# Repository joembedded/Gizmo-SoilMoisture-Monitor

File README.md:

# Gizmo - 'GiessMonitor' #
**Ein LowCost IoT Sensor zur Messung der Bodenfeuchte mit LoRa und/oder SDI-12/BluetoothLE**

Es gibt unzählige Ultra-LowCost-Sensoren zur Messung der Bodenfeuchte.
Die meisten davon taugen aber oft nicht einmal für Hobby-Zwecke.

Das Projekt Gizmo - 'GiessMonitor' möchte einen einfachen, aber trotzdem
für die Praxis geeigneten IoT Sensor entwickeln. Final soll ein LoRa-Modul
eingesetzt werden, so dass Gizmo auch über grosse Entfernungen und selbst mit
einfachen Batterien jahrelang arbeiten kann. 

_*Gizmo ist ein 100% Open Source Projekt!*_
_*Wenn alles klappt, könnte daraus ein spannender und preisgünstiger Sensor für die Allgemeinheit werden.*_
_*'Collaborteure' sind jederzeit herzlich willkommen!*_

---
**Gizmo_0V15 - Boilerplate und Vor-Prototyp**

Im ersten Schritt geht es aber erst einmal darum das Messverfahren festzulegen.

Es bietet sich an die recht hohe Dielektrizitätskonstante von Wasser auszunutzen. 
Diese ist bis ca. 1 GHz recht konstant (bei ca. 80), hat aber den Nachteil, dass z.B. Salze bei
niedereren Frequenzen (unter ca. 1-10 Mhz) das Signal stark verfälschen.
(Details dazu: [Permitivität von mineralisiertem Wasser](https://de.wikipedia.org/wiki/Permittivit%C3%A4t). Die Permitivität setzt sich aus der 
Dielektrizitätskonstante (Realteil) und dem störenden Leitwert (Imaginärteil) zusammen).

(Technische Anmerkung: Die Menge des vorhandenen Wassers im Boden ist allerdings trotzdem auch immer nur ein indirektes Mass für den 'Giess-Bedarf',
denn die Art des Bodens (z.B. sandig oder eher lehmig) spielt eine fast noch größere Rolle. Aber da diese sich lokal normalerweise nicht ändert,
ist der Wassergehalt als Messwert absolut OK. Auch ist der Salzgehalt nicht von Interesse, einzig nur sollte er das Signal möglichst wenig verfälschen.
Gizmo soll ja auch kein wissenschaftliches Messgerät, sondern nur ein (hoffentlich) zuverlässiger Giess-Monitor werden).

Es bietet sich also an, Frequenzen im Bereich > 10 Mhz und < 1Ghz zu verwenden. Als Sensorelement wird die Kapazität einer kleinen 
Kupferfläche (die in einer korrosionsgeschützten Innenlage der PCB geschützt ist) verwendet und ungefähr ca. 10pF - 80pF beträgt.
Je stärker das Anregungssignal ist, desto günstiger wird auch die Messung. Aber schnell kann daraus auch ein nicht CE-konformer Sender werden.

Nach wissenschaftlichen Referenzstudien vergleichbarer Sensoren (u.a. [Measurement of Soil Water Content with a 50-MHz Soil Dielectric Sensor](https://www.researchgate.net/publication/43261344_Measurement_of_Soil_Water_Content_with_a_50-MHz_Soil_Dielectric_Sensor) ) eignet sich das weltweit freie ISM-Band 40.660 – 40.700 MHz dazu sehr gut. In Deutschland sind hier bis zu 10 mW Sendeleistung erlaubt ([SRD Verfügung](https://www.bundesnetzagentur.de/SharedDocs/Downloads/DE/Sachgebiete/Telekommunikation/Unternehmen_Institutionen/Frequenzen/Allgemeinzuteilungen/FunkanlagenGeringerReichweite/2018_05_SRD_pdf.pdf?__blob=publicationFile&v=1)).

Die Geometrie der Sensorfläche muss für einen kapazitiven Sensor aber jedezeit unter der Lambda/4-Länge liegen, bei einer max. Dielektrizitätskonstante von 80 wären das bei 40 Mhz ca. 21 cm. Eine erste Simulation mit FEMM ergab ca. 10 cm als gut geeignet. Die Kupferflächen werden korrosionsgeschützt symetrisch auf den beiden Innenlagen platziert, Details zur Geometrie im Schaltplan.

[Sensorsimulation](./docu/sensorsim01.png) die erste mit FEMM simulierte Geometrie kam dem Ergebnis schon recht nahe.

Die Frage war auch, ob das 40 Mhz Signal störende Oberwellen abstrahlt (diese sind in der DIN EN 55011 / CISPR 11 definiert). Eine Freifeld-Messung ergab aber keinerlei Auffälligkeiten, selbst auf der Grundfrequenz ist die Abstrahlung noch leicht unterm allgemeinen Grenzwert, wenn also ein 40.68 MHz Oszillator verwendet wird, ist Gizmo in jedem Fall absolut im erlaubten Bereich (der Grenzwert für SRD ist bei ca. 105 dBµV/m): [EMV Bewertung](./docu/emv_girmo_pre.png).

  Die erste Version arbeitet mit SDI-12 und Bluetooth (Modul: [Open-SDI12-Blue](https://github.com/joembedded/Open-SDI12-Blue) )

[Gizmo_0V1 - PCB, Layouts und Schaltpläne im Ordner 'docu'](./docu/)

---
**Gizmo - der Plan**
- Tests und Festlegung des Messsystems: Dazu PCB mit SDI-12 und Bluetooth.
- Erste Software (basierend auf Open-SDI12-Blue-Libs und JesFs)
- Finalisierung V1.0 mit LoRa-Modul und 3D-gedrucktem Batteriefach
- Problemlose Anbindung an z.B. das Community LoRa-Netz TTN oder ChirpStack
- ...

---
## Changelog  ##
- 01.04.2023 V0.01 Gizmo Prototyp als PCB in Fertigung gegeben
- 07.04.2023 Erste elektrische Tests der PCB V0.01
- 15.05.2025 Gizmo V0.15 als SDI-12 Sensor und mit Bluetooth 
- 18.07.2025 RAK3172LP: erste Prototypen mit KiCAD Breakout-Board OK
---

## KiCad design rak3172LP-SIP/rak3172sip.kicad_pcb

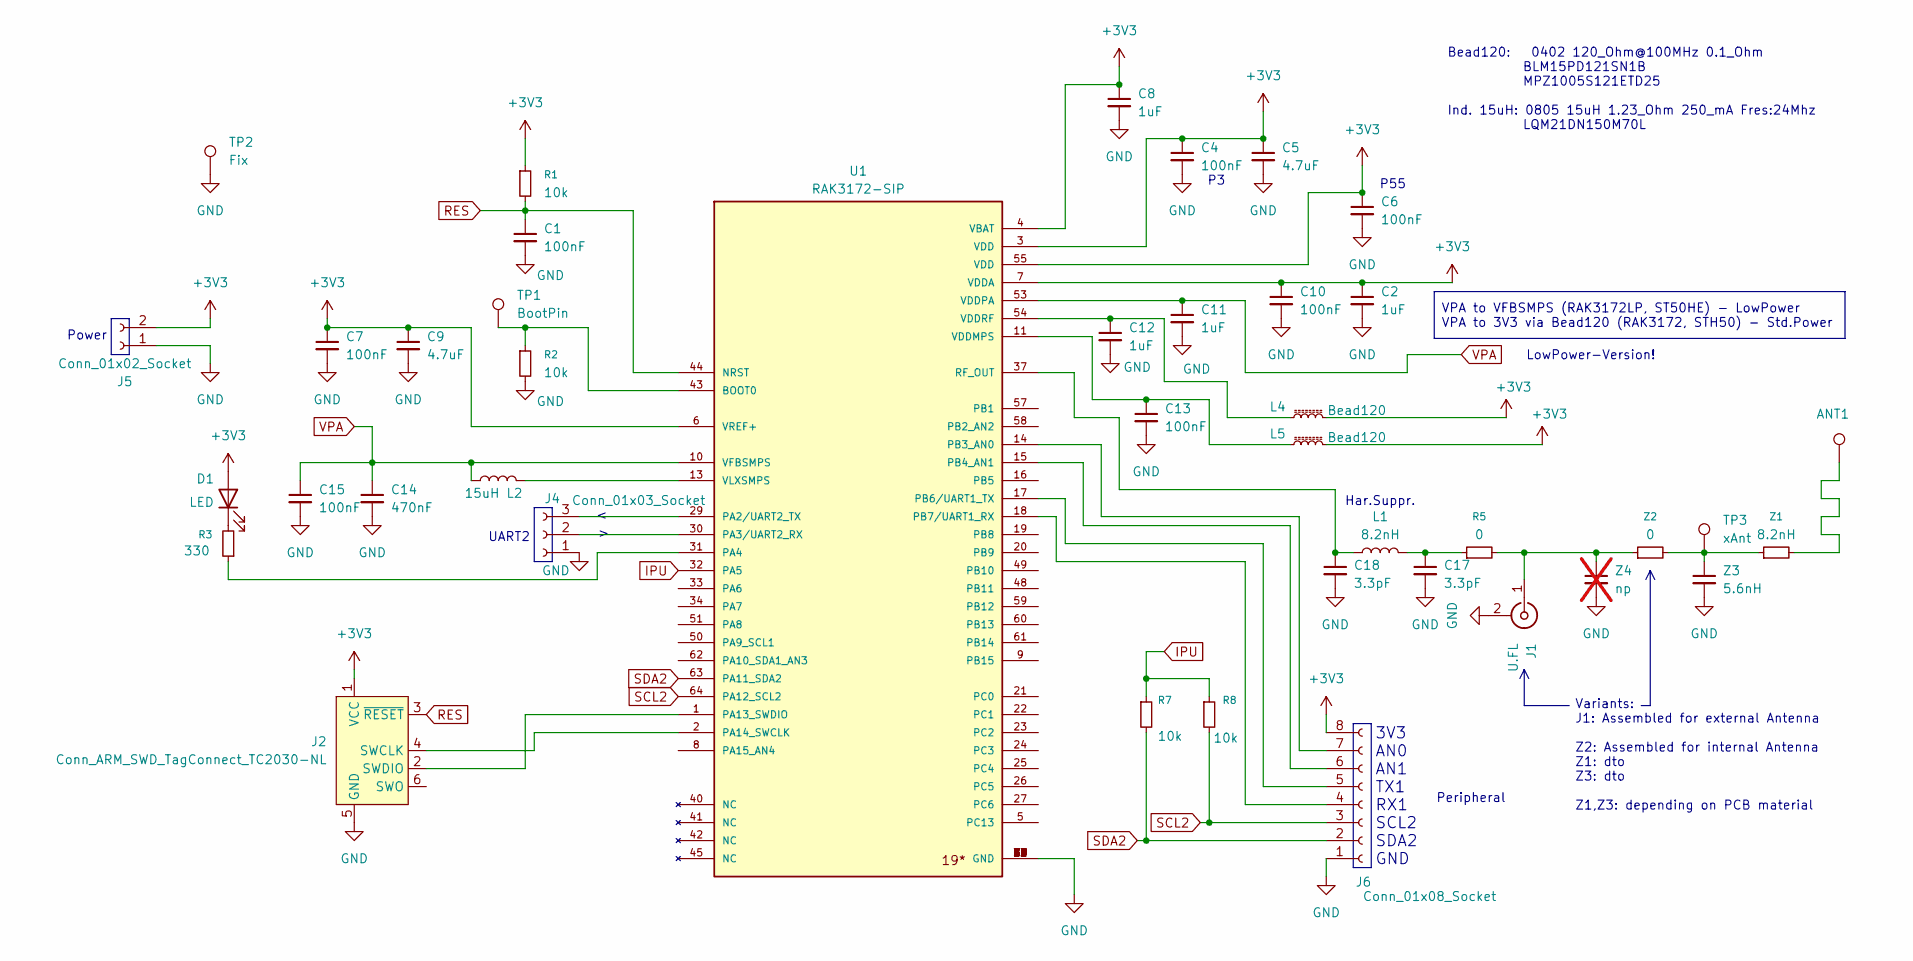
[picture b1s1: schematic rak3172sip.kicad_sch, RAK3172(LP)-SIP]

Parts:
ANT1: ANT; TestPoint_Pad_D1.0mm
C1, C4, C6, C7, C10, C13, C15: 100nF; C_0402_1005Metric
C2, C8, C11, C12: 1uF; C_0603_1608Metric
C5, C9: 4.7uF; C_0603_1608Metric
C14: 470nF; C_0603_1608Metric
C17, C18: 3.3pF; C_0402_1005Metric
D1: LED; LED_0603_1608Metric
J1: U.FL; U.FL_Hirose_U.FL-R-SMT-1_Vertical
J2: Conn_ARM_SWD_TagConnect_TC2030-NL; Tag-Connect_TC2030-IDC-NL_2x03_P1.27mm_Vertical
J4: Conn_01x03_Socket; PinHeader_1x03_P2.54mm_Vertical
J5: Conn_01x02_Socket; PinHeader_1x02_P2.54mm_Vertical
J6: Conn_01x08_Socket; PinHeader_1x08_P2.54mm_Vertical
L1: 8.2nH; L_0402_1005Metric
L2: 15uH; L_0805_2012Metric
L4, L5: Bead120; L_0402_1005Metric
R1, R2, R7, R8: 10k; R_0402_1005Metric
R3: 330; R_0402_1005Metric
R5: 0; R_0603_1608Metric
TP1: BootPin; PinHeader_1x01_P2.00mm_Vertical
TP2: Fix; TestPoint_Plated_Hole_D3.0mm
TP3: xAnt; PinHeader_1x01_P2.00mm_Vertical
U1: RAK3172-SIP; XCVR_RAK3172-SIP; PARTREV 3/15/2023
Z1: 8.2nH; R_0603_1608Metric
Z2: 0; R_0603_1608Metric
Z3: 5.6nH; C_0603_1608Metric
Z4: np; C_0603_1608Metric; not fitted

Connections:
+3V3: C2.1, C4.1, C5.1, C6.1, C7.1, C8.1, C9.1, C10.1, D1.2 (A), J2.1 (VCC), J5.2, J6.8, L4.2, L5.2, R1.1, U1.3 (VDD), U1.4 (VBAT), U1.6 (VREF+), U1.7 (VDDA), U1.55 (VDD)
GND: C1.2, C2.2, C4.2, C5.2, C6.2, C7.2, C8.2, C9.2, C10.2, C11.2, C12.2, C13.2, C14.2, C15.2, C17.2, C18.2, J1.2 (Ext), J2.5 (GND), J4.1, J5.1, J6.1, R2.2, TP2.1, U1.12 (GND), U1.28 (GND), U1.35 (GND), U1.36 (GND), U1.38 (GND), U1.39 (GND), U1.46 (GND), U1.47 (GND), U1.52 (GND), U1.56 (GND), U1.65 (GND), U1.66 (GND), U1.67 (GND), U1.68 (GND), U1.69 (GND), U1.70 (GND), U1.71 (GND), U1.72 (GND), U1.73 (GND), Z3.2, Z4.2
IPU: R7.1, R8.1, U1.32 (PA5)
unnamed: ANT1.1, Z1.2
unnamed: C17.1, L1.2, R5.1
unnamed: D1.1 (K), R3.2
unnamed: J1.1 (In), R5.2, Z2.1, Z4.1
unnamed: J2.4 (SWCLK), U1.2 (PA14_SWCLK)
unnamed: J2.2 (SWDIO), U1.1 (PA13_SWDIO)
unnamed: J4.2, U1.30 (PA3/UART2_RX)
unnamed: J4.3, U1.29 (PA2/UART2_TX)
unnamed: J6.4, U1.18 (PB7/UART1_RX)
unnamed: J6.5, U1.17 (PB6/UART1_TX)
unnamed: J6.6, U1.15 (PB4_AN1)
unnamed: J6.7, U1.14 (PB3_AN0)
unnamed: TP3.1, Z1.1, Z2.2, Z3.1
unnamed: R2.1, TP1.1, U1.43 (BOOT0)
unnamed: R3.1, U1.31 (PA4)
unnamed: C18.1, L1.1, U1.37 (RF_OUT)
unnamed: C13.1, L5.1, U1.11 (VDDMPS)
unnamed: C12.1, L4.1, U1.54 (VDDRF)
unnamed: L2.2, U1.13 (VLXSMPS)
RES: C1.1, J2.3 (~RESET), R1.2, U1.44 (NRST)
SCL2: J6.3, R8.2, U1.64 (PA12_SCL2)
SDA2: J6.2, R7.2, U1.63 (PA11_SDA2)
VPA: C11.1, C14.1, C15.1, L2.1, U1.10 (VFBSMPS), U1.53 (VDDPA)

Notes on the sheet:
Variants: J1: Assembled for external Antenna Z2: Assembled for internal Antenna Z1: dto Z3: dto Z1,Z3: depending on PCB material
Har.Suppr.
Power
Peripheral
UART2
3V3 AN0 AN1 TX1 RX1 SCL2 SDA2 GND
LowPower-Version!
Bead120: 0402 120_Ohm@100MHz 0.1_Ohm BLM15PD121SN1B MPZ1005S121ETD25 Ind. 15uH: 0805 15uH 1.23_Ohm 250_mA Fres:24Mhz LQM21DN150M70L
P55
VPA to VFBSMPS (RAK3172LP, ST50HE) - LowPower VPA to 3V3 via Bead120 (RAK3172, STH50) - Std.Power

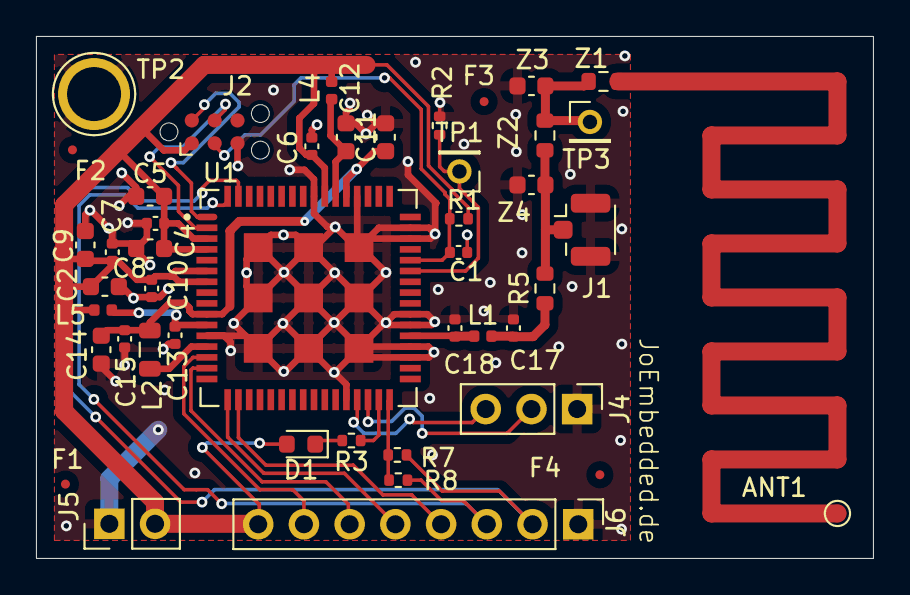
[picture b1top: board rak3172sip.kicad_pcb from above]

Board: 2 copper layers, 46.5 x 29.0 mm, 45 parts (0 on the bottom side), 26 nets.

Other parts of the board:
F1, F2, F3, F4: Fiducial_0.5mm_Mask1mm

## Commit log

2023-04-07 Tests PCB 0v1
2023-04-07 PCB 0V1 erste Tests
2025-05-07 V0.1 Verifiziert, SW OK, APP OK
2025-05-20 V0.15
2025-05-23 arduino_wrk
2025-05-25 RAK3172
2025-05-25 readme fuer ino
2025-05-27 ino V1.0
2025-05-27 LTX for Arduino V1.00
2025-05-27 INO Format
2025-05-28 Docu
2025-05-29 energy
2025-05-29 Arduino
2025-05-30 V1.0
2025-06-05 ATC+LTX wrk
2025-06-10 Standalone/XLTX
2025-06-10 EnergyWrk
2025-06-11 lib wrk
2025-06-11 testsw
2025-06-15 pcb rak3172
2025-06-17 0v02
2025-07-03 LTX_App V1.4
2025-07-07 LoRa wrk
2025-07-18 Rak3172LP V0.03
2025-08-19 Backups
2025-10-10 HW V0.04
2025-10-11 RUI_4.2.2
2025-10-12 0.04
2025-10-13 V1.8
2025-10-14 rak_1v8
